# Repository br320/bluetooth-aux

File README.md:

Bluetooth AUX

My phone doesn't have a headphone jack and my car doesn't have wireless/bluetooth. This is my solution. 
Plan for initial version powered via USB and later may move to using a battery if necessary.

`hardware` - kicad schematics and pcb files

`firmware` - esp32 firmware for board

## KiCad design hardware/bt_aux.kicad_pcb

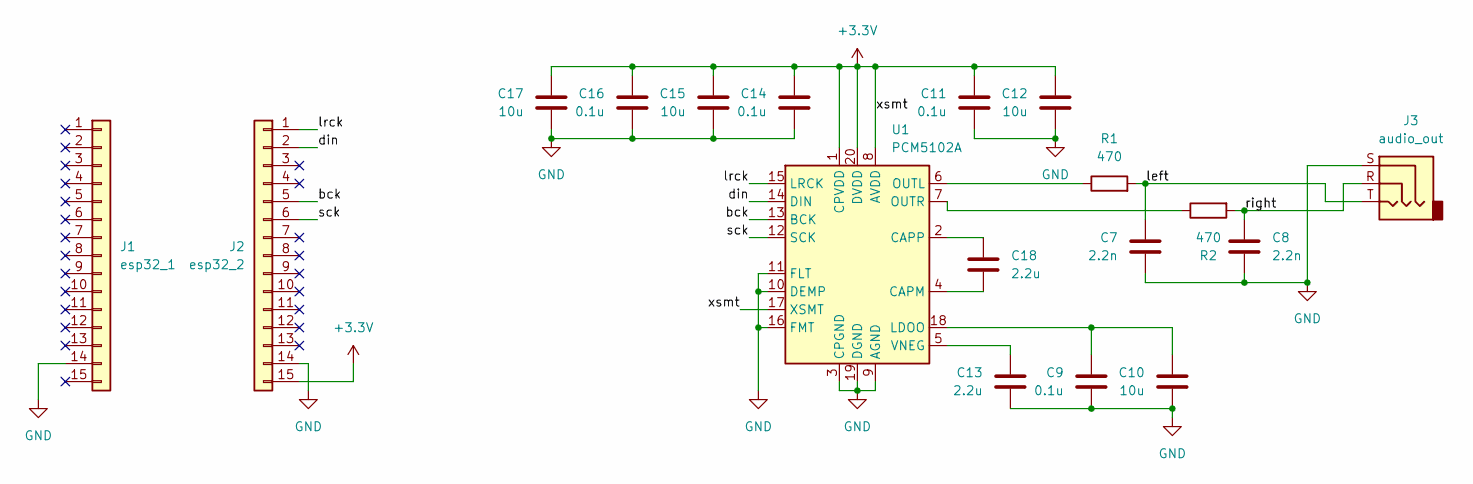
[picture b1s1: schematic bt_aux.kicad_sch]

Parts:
C7, C8: 2.2n; C_0805_2012Metric; LCSC C2875527
C9, C11, C14, C16: 0.1u; C_0805_2012Metric; LCSC C77456
C10, C12, C15, C17: 10u; C_0805_2012Metric; LCSC C84416
C13, C18: 2.2u; C_0805_2012Metric; LCSC C19110
J1: esp32_1; PinSocket_1x15_P2.54mm_Vertical; LCSC C2897378
J2: esp32_2; PinSocket_1x15_P2.54mm_Vertical; LCSC C2897378
J3: audio_out; BOOMELE_PJ-320B; LCSC C18594
R1, R2: 470; R_0805_2012Metric; LCSC C908864
U1: PCM5102A; TSSOP-20_4.4x6.5mm_P0.65mm; LCSC C107671

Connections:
+3.3V: C11.1, C12.1, C14.1, C15.1, C16.1, C17.1, J2.15, U1.1 (CPVDD), U1.8 (AVDD), U1.17 (XSMT), U1.20 (DVDD)
/bck: J2.5, U1.13 (BCK)
/din: J2.2, U1.14 (DIN)
/left: C7.1, J3.T, R1.2
/lrck: J2.1, U1.15 (LRCK)
/right: C8.1, J3.R, R2.2
/sck: J2.6, U1.12 (SCK)
GND: C7.2, C8.2, C9.2, C10.2, C11.2, C12.2, C13.2, C14.2, C15.2, C16.2, C17.2, J1.14, J2.14, J3.S, U1.3 (CPGND), U1.9 (AGND), U1.10 (DEMP), U1.11 (FLT), U1.16 (FMT), U1.19 (DGND)
unnamed: C18.2, U1.4 (CAPM)
unnamed: C18.1, U1.2 (CAPP)
unnamed: C9.1, C10.1, U1.18 (LDOO)
unnamed: R1.1, U1.6 (OUTL)
unnamed: R2.1, U1.7 (OUTR)
unnamed: C13.1, U1.5 (VNEG)

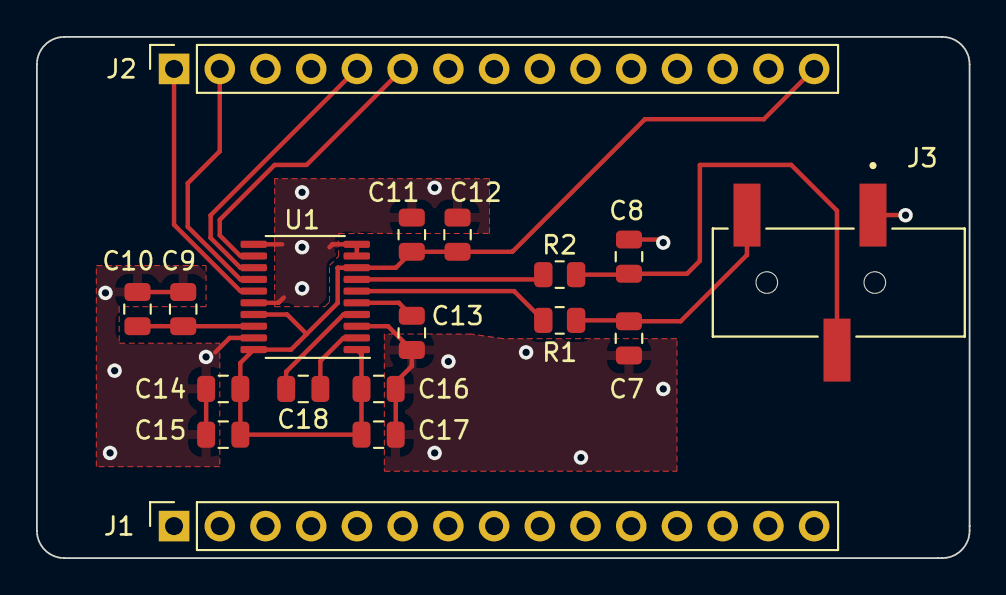
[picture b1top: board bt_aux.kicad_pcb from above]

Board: 2 copper layers, 51.8 x 29.0 mm, 18 parts (0 on the bottom side), 14 nets.

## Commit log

2023-12-16 initial schematic
2023-12-16 fix readme formatting
2023-12-17 update footprints, links, and price of components
2023-12-17 change xsmt connection direct to avdd instead of pullup
2023-12-17 initial layout aux and dac with components
2023-12-17 add copper pours and rest of connections to headers
2023-12-17 give pcb nice beautiful corners
2023-12-17 fix oreintation of jack
2023-12-17 modify bom, generate fab files, submit order
